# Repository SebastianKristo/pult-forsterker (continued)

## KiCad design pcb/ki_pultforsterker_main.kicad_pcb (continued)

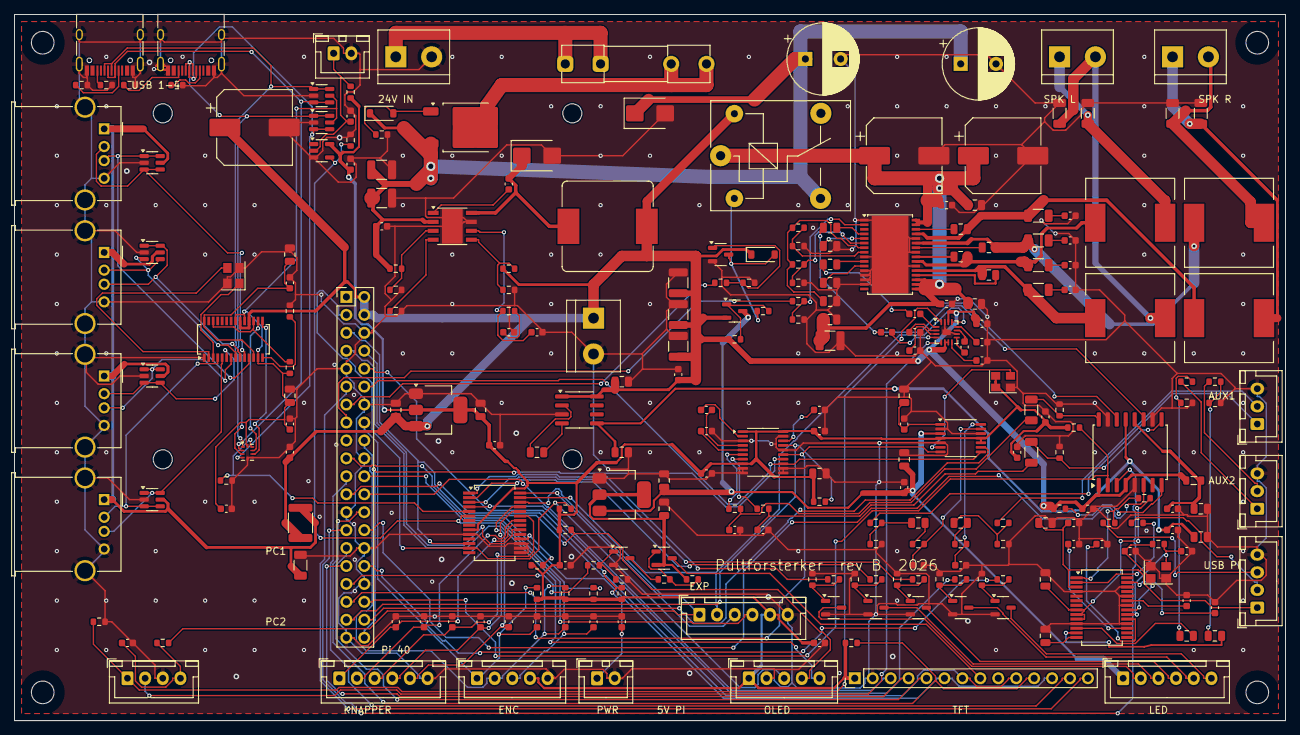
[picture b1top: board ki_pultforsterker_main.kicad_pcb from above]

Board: 2 copper layers, 180.0 x 100.0 mm, 264 parts (0 on the bottom side), 188 nets.

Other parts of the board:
H1, H2, H3, H4: M3; MountingHole_3.2mm_M3
H5, H6, H7, H8: M2.5; MountingHole_2.7mm_M2.5

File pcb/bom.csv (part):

Designator,Value,Footprint,LCSC,Beskrivelse
J1,24V IN,TerminalBlock_bornier-2_P5.08mm,C8465,"24 V inn fra DC-099 via KCD1 (skruterminal 5,08)"
F1,5A 5x20 (Littelfuse 111-klips),Fuseholder_Clip-5x20mm_Littelfuse_111_Inline_P20.00x5.00mm_D1.05mm_Horizontal,C151075,"Sikringsholder 5x20 (klips, THT) + sikring 5 A"
D1,SMBJ28A,D_SMB,C20623778,"TVS 28 V standoff, klemmer ~45 V (LCSC-kode sjekkes i BOM-verktøyet)"
Q11,AOD409,TO-252-2,C36220,"Polvendingsvern i 24 V-linjen (D = inn, S = ut, G mot GND) – velg TO-252 P-kanal ≥ 60 V i JLC-verktøyet"
D5,BZT52C12,D_SOD-123,C43491,Zener gate-source Q11
R79,100k,R_0603_1608Metric,C25803,Gate Q11 mot GND
C1,680-1000u/35V 10x16,CP_Radial_D10.0mm_P5.00mm,,"Bulk elektrolytt Ø10 × maks 16 mm (THT, loddes selv)"
C110,680-1000u/35V 10x16,CP_Radial_D10.0mm_P5.00mm,,Bulk elektrolytt nr. 2 (Ø10 × maks 16 mm)
J2,SPK L,TerminalBlock_bornier-2_P5.08mm,C8465,Høyttaler venstre + / -
J3,SPK R,TerminalBlock_bornier-2_P5.08mm,C8465,Høyttaler høyre + / -
K1,SRD-05VDC-SL-C,Relay_SPDT_SANYOU_SRD_Series_Form_C,C35449,"Relé 10 A: bryter 24 V til forsterkeren (KiCad-pads: 2+5 spole, 1 COM, 3 NO, 4 NC – mål før første gang!)"
Q7,AO3400A,SOT-23-3,C20917,Relédriver + styrer Q8
D4,1N4148W,D_SOD-123,C81598,Flyback relé
R52,100,R_0603_1608Metric,C22775,Gate Q7
R53,100k,R_0603_1608Metric,C25803,Gate pulldown Q7
Q8,AO3401A,SOT-23-3,C15127,P-MOSFET 5 V -> 5V_SW
R54,10k,R_0603_1608Metric,C25804,Q8 gate fra Q7
R55,100k,R_0603_1608Metric,C25803,Q8 gate pull-up
U1,TPS54560DDAR,Texas_HSOP-8-1EP_3.9x4.9mm_P1.27mm,C31966,Buck 60 V 5 A
C2,4.7u/50V,C_1210_3225Metric,C170099,Cin
C3,4.7u/50V,C_1210_3225Metric,C170099,Cin
C4,100n/50V,C_0603_1608Metric,C14663,Cin HF
C5,100n/50V,C_0603_1608Metric,C14663,Boot
R1,330k,R_0603_1608Metric,C23137,EN divider (UVLO ~9 V)
R2,49.9k,R_0603_1608Metric,C23184,EN divider
R3,243k,R_0603_1608Metric,C100895,RT 400 kHz
R4,33k,R_0603_1608Metric,C4216,"FB top (33k/6,2k -> 5,06 V)"
R5,6.2k,R_0603_1608Metric,C4260,"FB bottom (5,06 V)"
R6,13k,R_0603_1608Metric,C22797,Comp R
C6,3.3n,C_0603_1608Metric,C1613,Comp C
C7,47p,C_0603_1608Metric,C1671,Comp Cp
L1,10uH 6A SRP1245A-100M,L_Bourns_SRP1245A,C2042471,Buck-spole 10 µH – Bourns SRP1245A-100M (søk i JLC-UI; alternativ: CEC SMRH125-100M C241221 4 A på samme fotavtrykk)
D2,SS56,D_SMB,C4154973,Catch-diode 60 V 5 A
C8,47u/16V,C_1210_3225Metric,C77101,Cout
C9,47u/16V,C_1210_3225Metric,C77101,Cout
C10,47u/16V,C_1210_3225Metric,C77101,Cout
C11,100n/50V,C_0603_1608Metric,C14663,Cout HF
U2,AMS1117-3.3,SOT-223-3_TabPin2,C6186,"LDO 3,3 V (alltid på: MCP23017, pull-ups)"
C12,10u,C_0805_2012Metric,C15850,LDO in
C13,10u,C_0805_2012Metric,C15850,LDO out
C14,100n/50V,C_0603_1608Metric,C14663,LDO out HF
U3,LM2662MX,SOIC-8_3.9x4.9mm_P1.27mm,C129316,"Ladepumpe -5 V, 150 kHz (FC til V+), 200 mA"
C15,10u,C_0805_2012Metric,C15850,Flykondensator
C109,10u,C_0805_2012Metric,C15850,LM2662 inn
C16,10u,C_0805_2012Metric,C15850,-5 V ut
U9,AMS1117-3.3,SOT-223-3_TabPin2,C6186,"LDO 3,3 V_SW (DAC, ADC, OLED/TFT) fra 5V_SW"
C75,10u,C_0805_2012Metric,C15850,LDO_SW in
C76,10u,C_0805_2012Metric,C15850,LDO_SW out
J5,RPi 40-pin,PinHeader_2x20_P2.54mm_Vertical,C50980,Raspberry Pi 40-pin (flatkabel)
J6,5V -> PI,TerminalBlock_bornier-2_P5.08mm,C8465,"5 V til Pi 4 (18 AWG til header pinne 2/6). Står med pinnene i x = 82 – utenfor Pi-ens USB3-blokk (x 84,5–104,5 under kortet)"
U12,MCP23017-E/SS,SSOP-28_5.3x10.2mm_P0.65mm,C506653,"I2C I/O-ekspander 0x20: knapper, LED-ringer, USB-mux"
R56,10k,R_0603_1608Metric,C25804,MCP RESET pull-up
C74,100n/50V,C_0603_1608Metric,C14663,MCP VDD
R43,4.7k,R_0603_1608Metric,C23162,I2C pull-up SDA
R44,4.7k,R_0603_1608Metric,C23162,I2C pull-up SCL
U4,PCM5102APWR,TSSOP-20_4.4x6.5mm_P0.65mm,C107671,I2S-DAC
C17,2.2u,C_0603_1608Metric,C23630,CAPP-CAPM
C18,2.2u,C_0603_1608Metric,C23630,VNEG
C19,2.2u,C_0603_1608Metric,C23630,LDOO
C20,100n/50V,C_0603_1608Metric,C14663,DVDD
C21,100n/50V,C_0603_1608Metric,C14663,AVDD/CPVDD
C22,10u,C_0805_2012Metric,C15850,3V3 bulk DAC
R7,10k,R_0603_1608Metric,C25804,XSMT pull-up
R8,100,R_0603_1608Metric,C22775,DAC L serie
R9,100,R_0603_1608Metric,C22775,DAC R serie
C23,2.2n/50V,C_0603_1608Metric,C1604,DAC L LP
C24,2.2n/50V,C_0603_1608Metric,C1604,DAC R LP
U10,PCM1808PWR,TSSOP-14_4.4x5mm_P0.65mm,C55513,"I2S-ADC AUX 1, master 256 fs (MD1=MD0=1, FMT=0)"
X1,12.288MHz,Oscillator_SMD_Abracon_ASE-4Pin_3.2x2.5mm,C437124,"Oscillator 3,3 V -> SCKI (48 kHz)"
C77,100n/50V,C_0603_1608Metric,C14663,Osc VDD
C78,10u,C_0805_2012Metric,C15850,VREF
C79,100n/50V,C_0603_1608Metric,C14663,VREF HF
C80,10u,C_0805_2012Metric,C15850,ADC VCC
C81,100n/50V,C_0603_1608Metric,C14663,ADC VCC HF
C82,100n/50V,C_0603_1608Metric,C14663,ADC VDD
R57,10k,R_0603_1608Metric,C25804,AUX1 L deler
R58,10k,R_0603_1608Metric,C25804,AUX1 L deler GND
R59,10k,R_0603_1608Metric,C25804,AUX1 R deler
R60,10k,R_0603_1608Metric,C25804,AUX1 R deler GND
C83,4.7u,C_0805_2012Metric,C1779,AUX1 L kobling
C84,4.7u,C_0805_2012Metric,C1779,AUX1 R kobling
R61,1k,R_0603_1608Metric,C21190,AUX1 L serie
R62,1k,R_0603_1608Metric,C21190,AUX1 R serie
C85,1n,C_0603_1608Metric,C1588,AUX1 L LP
C86,1n,C_0603_1608Metric,C1588,AUX1 R LP
C25,10u,C_1206_3216Metric,C13585,Kobling L
C26,10u,C_1206_3216Metric,C13585,Kobling R
R12,100k,R_0603_1608Metric,C25803,Bias L
R13,100k,R_0603_1608Metric,C25803,Bias R
U5,PGA2311UA,SOIC-16W_7.5x10.3mm_P1.27mm,C486061,Volumkontroll ±5 V
C27,100n/50V,C_0603_1608Metric,C14663,VD+
C28,100n/50V,C_0603_1608Metric,C14663,VA+
C29,100n/50V,C_0603_1608Metric,C14663,VA-
C30,10u,C_0805_2012Metric,C15850,VA+ bulk
C31,10u,C_0805_2012Metric,C15850,VA- bulk
FB1,600R@100MHz,L_0805_2012Metric,C18305,Ferritt 5V_SW -> PGA2311 VA+ (filter)
R14,10k,R_0603_1608Metric,C25804,MUTE pull-up
U6,TPA3116D2DADR,HTSSOP-32-1EP_6.1x11mm_P0.65mm_EP5.2x11mm_Mask4.11x4.36mm,C50144,Klasse D 2x50 W (kjøleflate på toppen – kjøleribbe!)
C32,220n/50V,C_0805_2012Metric,C5378,"BSNL (snudd: OUTNL rett inn i pad 2, BSNL rundt under)"
C33,220n/50V,C_0805_2012Metric,C5378,BSPL
C34,220n/50V,C_0805_2012Metric,C5378,BSNR
C35,220n/50V,C_0805_2012Metric,C5378,BSPR
C36,100n/50V,C_0603_1608Metric,C14663,PVCC HF
C37,1u/50V,C_0805_2012Metric,C28323,PVCC
C38,100n/50V,C_0603_1608Metric,C14663,PVCC HF
C39,1u/50V,C_0805_2012Metric,C28323,PVCC
C40,220u/50V,CP_Elec_10x10.5,C190286,PVCC bulk
C41,220u/50V,CP_Elec_10x10.5,C190286,PVCC bulk
C42,1u/50V,C_0805_2012Metric,C28323,AVCC
C43,4.7u/50V,C_1210_3225Metric,C170099,AVCC bulk
C44,1u/50V,C_0805_2012Metric,C28323,GVDD
R15,100k,R_0603_1608Metric,C25803,GAIN top
R16,20k,R_0603_1608Metric,C4184,GAIN bottom (26 dB)
R17,0R,R_0603_1608Metric,C21189,PLIMIT -> GVDD (ingen begrensning)
R18,DNP,R_0603_1608Metric,,PLIMIT til GND (valgfri)
R19,1k,R_0603_1608Metric,C21190,SDZ serie
R20,100k,R_0603_1608Metric,C25803,SDZ pulldown
C45,1u/50V,C_0805_2012Metric,C28323,LINP kobling
C46,1u/50V,C_0805_2012Metric,C28323,LINN til GND
C47,1u/50V,C_0805_2012Metric,C28323,RINP kobling
C48,1u/50V,C_0805_2012Metric,C28323,RINN til GND
L2,10uH 5.5A,L_12x12mm_H8mm,C3221699,Utgangsfilter OUTNL
L3,10uH 5.5A,L_12x12mm_H8mm,C3221699,Utgangsfilter OUTPL
L4,10uH 5.5A,L_12x12mm_H8mm,C3221699,Utgangsfilter OUTNR
L5,10uH 5.5A,L_12x12mm_H8mm,C3221699,Utgangsfilter OUTPR
C49,680n/50V,C_1206_3216Metric,C1881,Filter OUTNL
C50,680n/50V,C_1206_3216Metric,C1881,Filter OUTPL
C51,680n/50V,C_1206_3216Metric,C1881,Filter OUTNR
C52,680n/50V,C_1206_3216Metric,C1881,Filter OUTPR
R21,18R,R_1206_3216Metric,C2907439,Snubber NL
C53,330p/50V,C_0603_1608Metric,C1664,Snubber NL
R22,18R,R_1206_3216Metric,C2907439,Snubber PL
C54,330p/50V,C_0603_1608Metric,C1664,Snubber PL
R23,18R,R_1206_3216Metric,C2907439,Snubber NR
C55,330p/50V,C_0603_1608Metric,C1664,Snubber NR
R24,18R,R_1206_3216Metric,C2907439,Snubber PR
C56,330p/50V,C_0603_1608Metric,C1664,Snubber PR
U11,PCM2900CDB,SSOP-28_5.3x10.2mm_P0.65mm,C180425,USB-lydkodek AUX 2 (ADC)
Y2,12MHz,Crystal_SMD_3225-4Pin_3.2x2.5mm,C9002,Kodek-krystall
C87,22p,C_0603_1608Metric,C1653,XTI last
C88,22p,C_0603_1608Metric,C1653,XTO last
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
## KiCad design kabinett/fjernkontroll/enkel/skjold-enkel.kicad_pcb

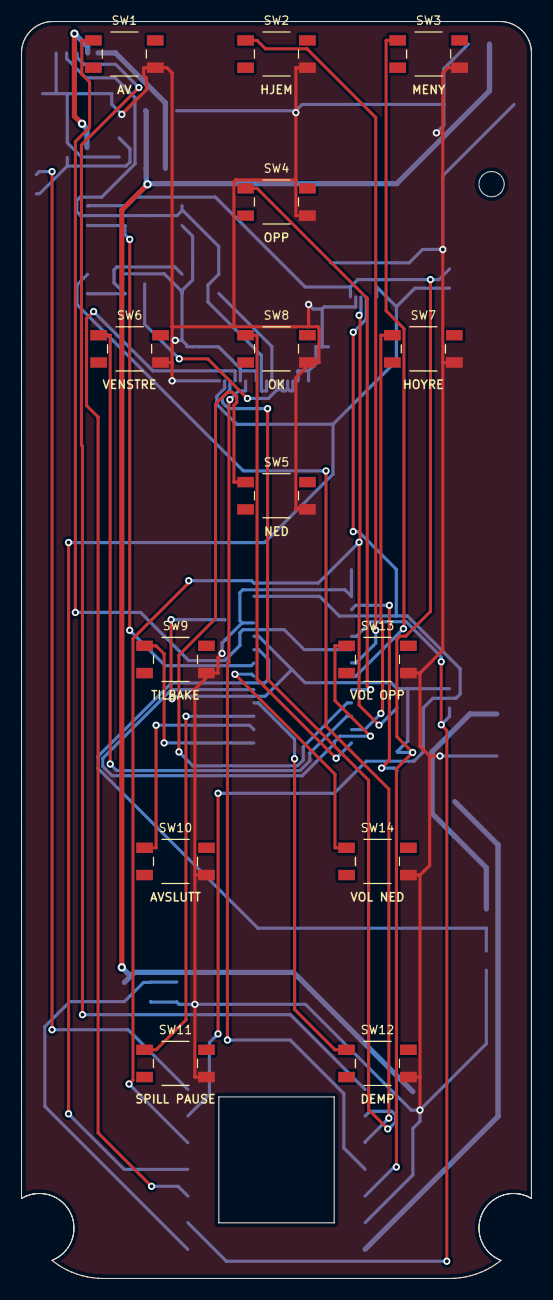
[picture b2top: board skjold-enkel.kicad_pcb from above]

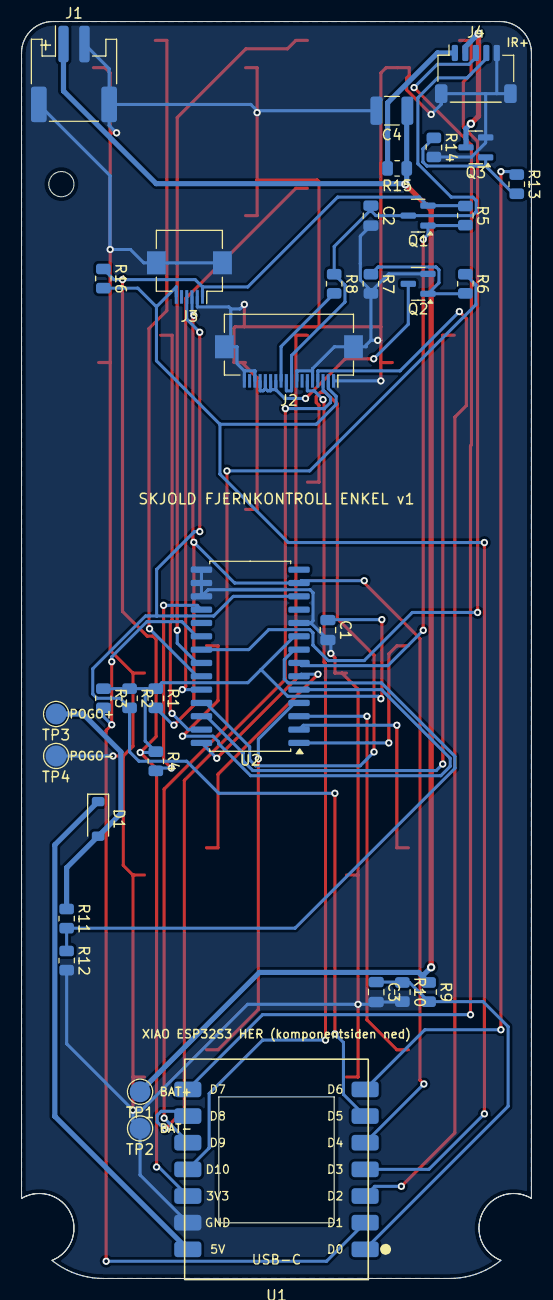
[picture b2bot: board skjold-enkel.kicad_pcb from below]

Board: 2 copper layers, 48.6 x 119.8 mm, 48 parts (34 on the bottom side), 40 nets.

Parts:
C1, C3: 100nF; C_0805_2012Metric
C2: 10uF; C_0805_2012Metric
C4: 100uF; C_1210_3225Metric
D1: B5819W; D_SOD-123
J1: S2B-PH-SM4-TB; JST_PH_S2B-PH-SM4-TB_1x02-1MP_P2.00mm_Horizontal
J2: FH12-18S-0.5SH; Hirose_FH12-18S-0.5SH_1x18-1MP_P0.50mm_Horizontal
J3: FH12-6S-0.5SH; Hirose_FH12-6S-0.5SH_1x06-1MP_P0.50mm_Horizontal
J4: SM05B-SRSS-TB; JST_SH_SM05B-SRSS-TB_1x05-1MP_P1.00mm_Horizontal
Q1: AO3401A; SOT-23
Q2, Q3: AO3400A; SOT-23
R1, R2: 4.7k; R_0805_2012Metric
R3, R4: 10k; R_0805_2012Metric
R5, R7, R12, R14: 100k; R_0805_2012Metric
R6, R13: 100R; R_0805_2012Metric
R8: 10R; R_0805_2012Metric
R9, R10, R16: 1M; R_0805_2012Metric
R11: 68k; R_0805_2012Metric
R15: 6.8R; R_0805_2012Metric
SW1, SW2, SW3, SW4, SW5, SW6, SW7, SW8, SW9, SW10, SW11, SW12, SW13, SW14: 4x4x1.5; SW_Tact_4x4x1.5mm_SMD
TP1: BAT+; TestPoint_Pad_D2.0mm
TP2: BAT-; TestPoint_Pad_D2.0mm
TP3: POGO+; TestPoint_Pad_D2.0mm
TP4: POGO-; TestPoint_Pad_D2.0mm
U1: XIAO_ESP32S3; Seeed_XIAO_ESP32S3_SMD
U2: MCP23017-E/SO; SOIC-28W_7.5x17.9mm_P1.27mm

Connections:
3V3: C1.1, J3.1, Q1.2, R1.1, R2.1, R3.1, R4.1, R5.1, R16.1, U1.12, U2.9
3V3_SW: C2.1, J2.9, J2.10, J4.4, Q1.3, R8.1
BL_G: Q2.1, R6.2, R7.1
DOKK: R11.2, R12.1, U2.8
GND: C1.2, C2.2, C3.2, C4.2, J1.2, J1.MP, J2.1, J2.5, J2.8, J2.16, J2.18, J2.MP, J3.2, J3.MP, J4.5, J4.MP, Q2.2, Q3.2, R7.2, R10.2, R12.2, R14.2, SW1.2, SW2.2, SW3.2, SW4.2, SW5.2, SW6.2, SW7.2, SW8.2, SW9.2, SW10.2, SW11.2, SW12.2, SW13.2, SW14.2, TP2.1, TP4.1, U1.13, U2.10, U2.15, U2.16, U2.17
INT: R3.2, U1.2, U2.20
IR_A: J4.1, R15.2
IR_G: Q3.1, R13.2, R14.1
IR_K: J4.2, Q3.3
IR_RX: J4.3, U1.8
IR_TX: R13.1, U1.7
K_AV: SW1.1, U2.21
K_AVSLUTT: SW10.1, U2.2
K_DEMP: SW12.1, U2.4
K_HJEM: SW2.1, U2.22
K_HOYRE: SW7.1, U2.27
K_MENY: SW3.1, U2.23
K_NED: SW5.1, U2.25
K_OK: SW8.1, U2.28
K_OPP: SW4.1, U2.24
K_SPILL_PAUSE: SW11.1, U2.3
K_TILBAKE: SW9.1, U2.1
K_VENSTRE: SW6.1, U2.26
K_VOL_NED: SW14.1, U2.6
K_VOL_OPP: SW13.1, U2.5
LCD_BL: R6.1, U1.10
LCD_DC: J2.4, U1.3
LCD_MOSI: J2.6, U1.11
LCD_RES: J2.2, J3.6, R16.2, U1.4
LCD_SCK: J2.3, U1.9
LED_A: J2.11, R8.2
LED_K: J2.12, J2.13, J2.14, J2.15, Q2.3
MCP_RST: R4.2, U2.18
POGO: D1.2, R11.1, TP3.1
SCL: J3.4, R2.2, U1.6, U2.12
SDA: J3.3, R1.2, U1.5, U2.13
SKJ: Q1.1, R5.2, U2.7
VBAT: C4.1, J1.1, R9.1, R15.1, TP1.1
VBAT_ADC: C3.1, R9.2, R10.1, U1.1
VBUS: D1.1, U1.14

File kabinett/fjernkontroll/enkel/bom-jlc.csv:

Comment,Designator,Footprint,LCSC Part #
100nF,"C1,C3",C_0805_2012Metric,C49678 (sjekk)
10uF,C2,C_0805_2012Metric,C15850 (sjekk)
100uF,C4,C_1210_3225Metric,sjekk: søk «100uF C»
B5819W,D1,D_SOD-123,C8598 (sjekk)
S2B-PH-SM4-TB,J1,JST_PH_S2B-PH-SM4-TB_1x02-1MP_P2.00mm_Horizontal,sjekk: søk «S2B-PH-SM4-TB JST»
FH12-18S-0.5SH,J2,Hirose_FH12-18S-0.5SH_1x18-1MP_P0.50mm_Horizontal,sjekk: søk «FH12-18S-0.5SH Hirose»
FH12-6S-0.5SH,J3,Hirose_FH12-6S-0.5SH_1x06-1MP_P0.50mm_Horizontal,sjekk: søk «FH12-6S-0.5SH Hirose»
SM05B-SRSS-TB,J4,JST_SH_SM05B-SRSS-TB_1x05-1MP_P1.00mm_Horizontal,sjekk: søk «SM05B-SRSS-TB JST»
AO3401A,Q1,SOT-23,C15127 (sjekk)
AO3400A,"Q2,Q3",SOT-23,C20917 (sjekk)
4.7k,"R1,R2",R_0805_2012Metric,C17673 (sjekk)
68k,R11,R_0805_2012Metric,C17801 (sjekk)
100k,"R5,R7,R12,R14",R_0805_2012Metric,C17407 (sjekk)
100R,"R6,R13",R_0805_2012Metric,C17408 (sjekk)
6.8R,R15,R_0805_2012Metric,sjekk: søk «6.8R R»
10k,"R3,R4",R_0805_2012Metric,C17414 (sjekk)
10R,R8,R_0805_2012Metric,C17415 (sjekk)
1M,"R9,R10,R16",R_0805_2012Metric,C17514 (sjekk)
MCP23017-E/SO,U2,SOIC-28W_7.5x17.9mm_P1.27mm,sjekk: søk «MCP23017-E/SO SOIC-28W»

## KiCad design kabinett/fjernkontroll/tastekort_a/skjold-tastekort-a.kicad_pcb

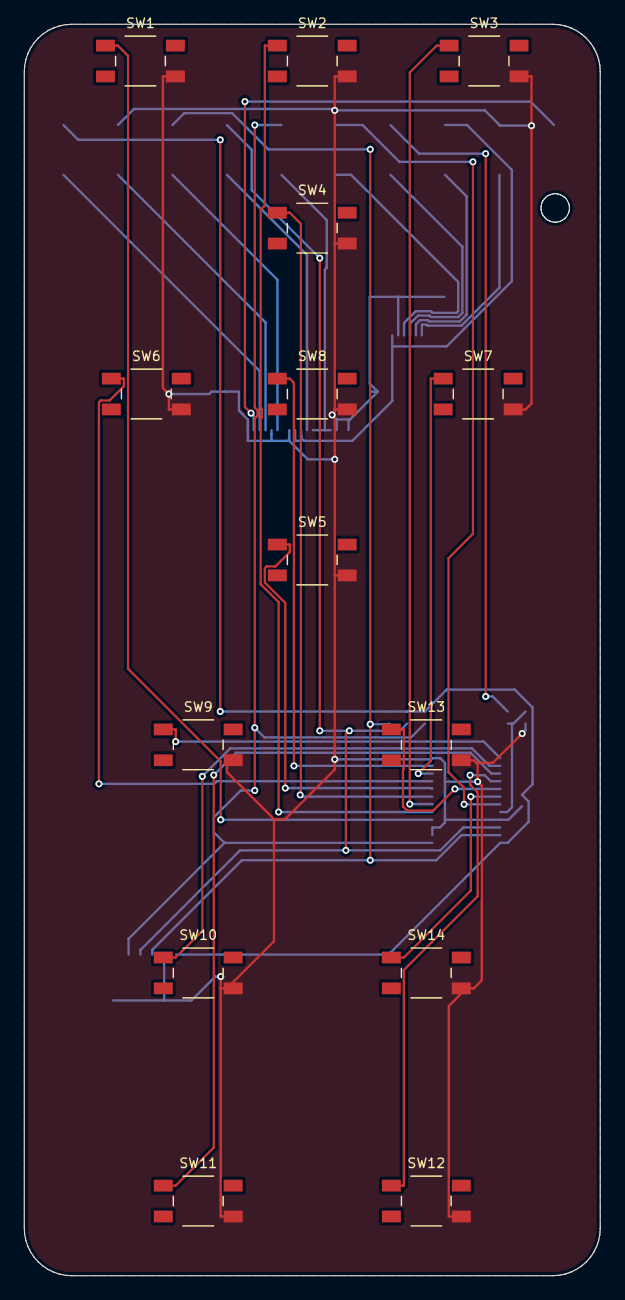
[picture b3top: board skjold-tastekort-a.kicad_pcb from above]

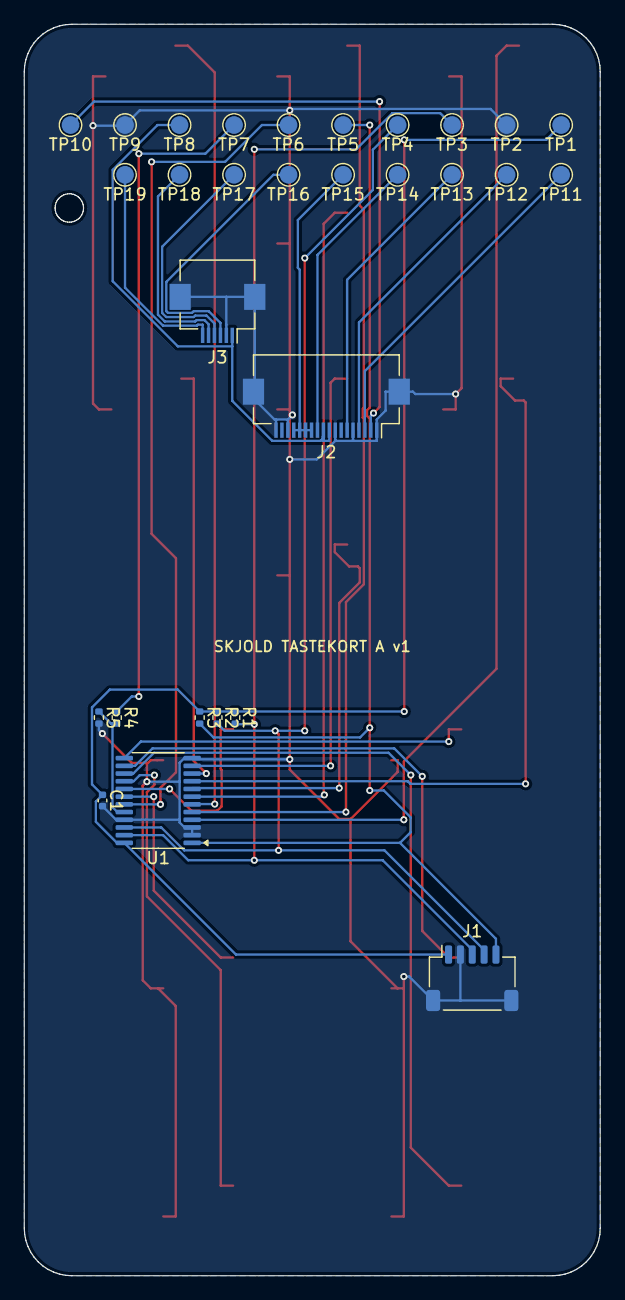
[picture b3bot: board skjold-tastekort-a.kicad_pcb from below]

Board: 2 copper layers, 48.6 x 105.6 mm, 43 parts (29 on the bottom side), 33 nets.

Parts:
C1: 100nF; C_0402_1005Metric
J1: SM05B-SRSS-TB; JST_SH_SM05B-SRSS-TB_1x05-1MP_P1.00mm_Horizontal
J2: FH12-18S-0.5SH; Hirose_FH12-18S-0.5SH_1x18-1MP_P0.50mm_Horizontal
J3: FH12-6S-0.5SH; Hirose_FH12-6S-0.5SH_1x06-1MP_P0.50mm_Horizontal
R1, R2, R3: 10k; R_0402_1005Metric
R4: 68k; R_0402_1005Metric
R5: 100k; R_0402_1005Metric
SW1, SW2, SW3, SW4, SW5, SW6, SW7, SW8, SW9, SW10, SW11, SW12, SW13, SW14: 4x4x1.5; SW_Tact_4x4x1.5mm_SMD
TP1: 3V3; TestPoint_Pad_D1.5mm
TP2, TP9: GND; TestPoint_Pad_D1.5mm
TP3: SDA; TestPoint_Pad_D1.5mm
TP4: SCL; TestPoint_Pad_D1.5mm
TP5: INT; TestPoint_Pad_D1.5mm
TP6: SKJ; TestPoint_Pad_D1.5mm
TP7: POGO+; TestPoint_Pad_D1.5mm
TP8: VCC; TestPoint_Pad_D1.5mm
TP10: LCD_RES; TestPoint_Pad_D1.5mm
TP11: LCD_SCK; TestPoint_Pad_D1.5mm
TP12: LCD_DC; TestPoint_Pad_D1.5mm
TP13: LCD_MOSI; TestPoint_Pad_D1.5mm
TP14: LED_A; TestPoint_Pad_D1.5mm
TP15: LED_K; TestPoint_Pad_D1.5mm
TP16: T_SDA; TestPoint_Pad_D1.5mm
TP17: T_SCL; TestPoint_Pad_D1.5mm
TP18: T_INT; TestPoint_Pad_D1.5mm
TP19: T_RST; TestPoint_Pad_D1.5mm
U1: TCA9555PWR; TSSOP-24_4.4x7.8mm_P0.65mm

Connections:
3V3: C1.1, J1.1, R1.1, R2.1, R3.1, TP1.1, U1.24
DOKK: R4.2, R5.1, U1.20
GND: C1.2, J1.2, J1.MP, J2.1, J2.5, J2.8, J2.16, J2.18, J2.MP, J3.2, J3.MP, R5.2, SW1.2, SW2.2, SW3.2, SW4.2, SW5.2, SW6.2, SW7.2, SW8.2, SW9.2, SW10.2, SW11.2, SW12.2, SW13.2, SW14.2, TP2.1, TP9.1, U1.2, U1.3, U1.12, U1.21
INT: J1.5, R3.2, TP5.1, U1.1
K_AV: SW1.1, U1.4
K_AVSLUTT: SW10.1, U1.14
K_DEMP: SW12.1, U1.16
K_HJEM: SW2.1, U1.5
K_HOYRE: SW7.1, U1.10
K_MENY: SW3.1, U1.6
K_NED: SW5.1, U1.8
K_OK: SW8.1, U1.11
K_OPP: SW4.1, U1.7
K_SPILL_PAUSE: SW11.1, U1.15
K_TILBAKE: SW9.1, U1.13
K_VENSTRE: SW6.1, U1.9
K_VOL_NED: SW14.1, U1.18
K_VOL_OPP: SW13.1, U1.17
LCD_DC: J2.4, TP12.1
LCD_MOSI: J2.6, TP13.1
LCD_RES: J2.2, TP10.1
LCD_SCK: J2.3, TP11.1
LED_A: J2.11, TP14.1
LED_K: J2.12, J2.13, J2.14, J2.15, TP15.1
POGO: R4.1, TP7.1
SCL: J1.4, R2.2, TP4.1, U1.22
SDA: J1.3, R1.2, TP3.1, U1.23
SKJ: TP6.1, U1.19
T_INT: J3.5, TP18.1
T_RST: J3.6, TP19.1
T_SCL: J3.4, TP17.1
T_SDA: J3.3, TP16.1
VCC_SKJ: J2.9, J2.10, J3.1, TP8.1

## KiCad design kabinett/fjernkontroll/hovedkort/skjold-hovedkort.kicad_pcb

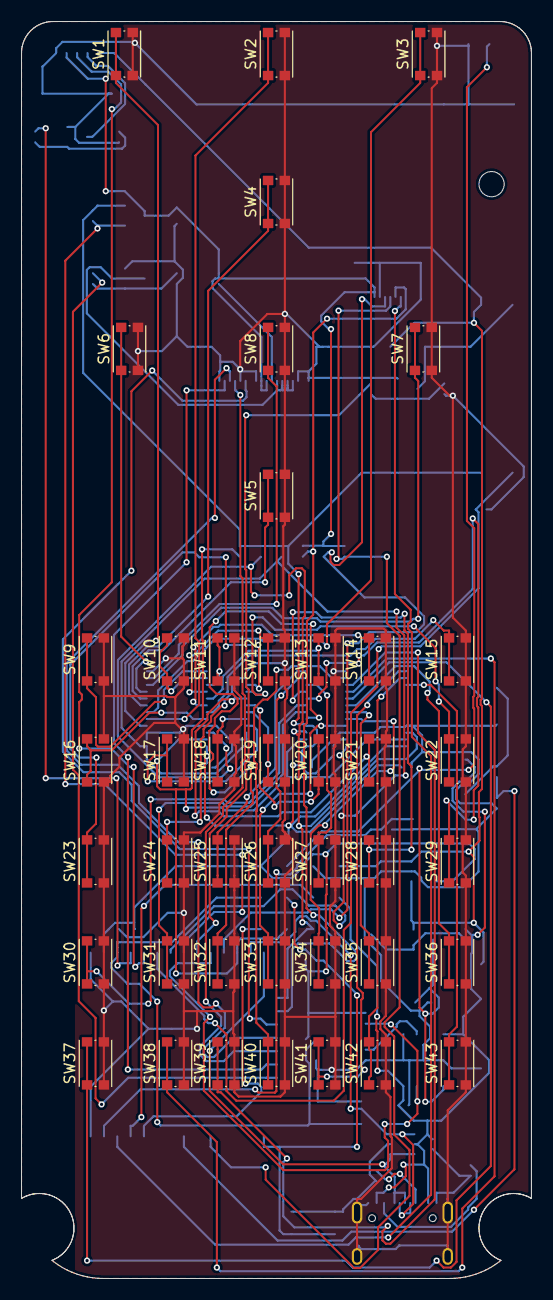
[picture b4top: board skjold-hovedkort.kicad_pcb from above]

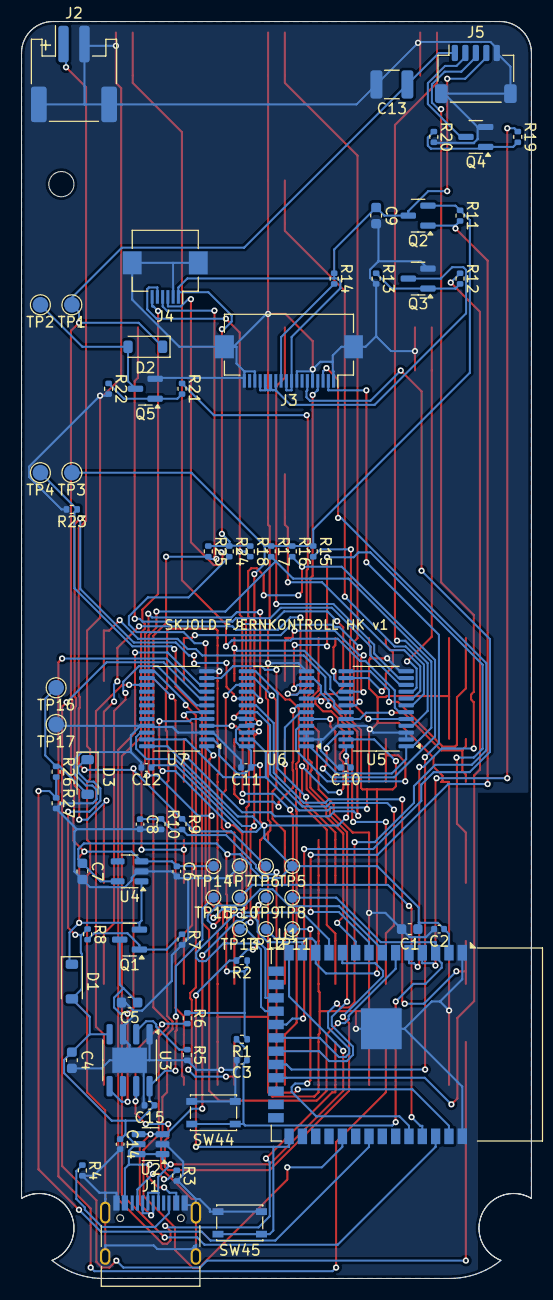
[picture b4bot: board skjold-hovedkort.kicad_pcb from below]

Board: 2 copper layers, 48.6 x 119.8 mm, 124 parts (81 on the bottom side), 87 nets.

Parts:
C1, C4, C5, C7, C9: 10uF; C_0603_1608Metric
C2, C8, C10, C11, C12, C14, C15: 100nF; C_0402_1005Metric
C3, C6: 1uF; C_0402_1005Metric
C13: 100uF; C_1210_3225Metric
D1, D2, D3: B5819W; D_SOD-123
J1: TYPE-C-31-M-12; USB_C_Receptacle_HRO_TYPE-C-31-M-12
J2: S2B-PH-SM4-TB; JST_PH_S2B-PH-SM4-TB_1x02-1MP_P2.00mm_Horizontal
J3: FH12-18S-0.5SH; Hirose_FH12-18S-0.5SH_1x18-1MP_P0.50mm_Horizontal
J4: FH12-6S-0.5SH; Hirose_FH12-6S-0.5SH_1x06-1MP_P0.50mm_Horizontal
J5: SM05B-SRSS-TB; JST_SH_SM05B-SRSS-TB_1x05-1MP_P1.00mm_Horizontal
Q1, Q2: AO3401A; SOT-23
Q3, Q4, Q5: AO3400A; SOT-23
R1, R2, R6, R17, R18: 10k; R_0402_1005Metric
R3, R4: 5.1k; R_0402_1005Metric
R5: 2.4k; R_0402_1005Metric
R7, R11, R13, R20, R22, R27: 100k; R_0402_1005Metric
R8: 0R; R_0402_1005Metric
R9, R10, R23: 1M; R_0402_1005Metric
R12, R19: 100R; R_0402_1005Metric
R14: 10R; R_0402_1005Metric
R15, R16, R24, R25: 4.7k; R_0402_1005Metric
R21: 1k; R_0402_1005Metric
R26: 68k; R_0402_1005Metric
SW1, SW2, SW3, SW4, SW5, SW6, SW7, SW8, SW9, SW10, SW11, SW12, SW13, SW14, SW15, SW16, SW17, SW18, SW19, SW20, SW21, SW22, SW23, SW24, SW25, SW26, SW27, SW28, SW29, SW30, SW31, SW32, SW33, SW34, SW35, SW36, SW37, SW38, SW39, SW40, SW41, SW42, SW43: KMR221G; SW_Push_1P1T_NO_CK_KMR2
SW44: PTS810 RESET; SW_SPST_PTS810
SW45: PTS810 BOOT; SW_SPST_PTS810
TP1: MOT+; TestPoint_Pad_D1.5mm
TP2: MOT-; TestPoint_Pad_D1.5mm
TP3: VIB 3V3; TestPoint_Pad_D1.5mm
TP4: VIB; TestPoint_Pad_D1.5mm
TP5: 3V3; TestPoint_Pad_D1.0mm
TP6: VBAT; TestPoint_Pad_D1.0mm
TP7: GND; TestPoint_Pad_D1.0mm
TP8: EN; TestPoint_Pad_D1.0mm
TP9: BOOT; TestPoint_Pad_D1.0mm
TP10: U0TXD; TestPoint_Pad_D1.0mm
TP11: U0RXD; TestPoint_Pad_D1.0mm
TP12: SDA; TestPoint_Pad_D1.0mm
TP13: SCL; TestPoint_Pad_D1.0mm
TP14: VSYS; TestPoint_Pad_D1.0mm
TP15: VBUS; TestPoint_Pad_D1.0mm
TP16: POGO+; TestPoint_Pad_D1.5mm
TP17: POGO-; TestPoint_Pad_D1.5mm
U1: ESP32-S3-WROOM-1-N4R2; ESP32-S3-WROOM-1
U2: USBLC6-2SC6; SOT-23-6
U3: TP4056; SOIC-8-1EP_3.9x4.9mm_P1.27mm_EP2.41x3.3mm
U4: RT9080-33GJ5; SOT-23-5
U5, U6, U7: TCA9555PWR; TSSOP-24_4.4x7.8mm_P0.65mm

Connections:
3V3: C1.1, C2.1, C7.1, C10.1, C11.1, C12.1, Q2.2, R1.1, R2.1, R6.1, R11.1, R15.1, R16.1, R17.1, TP3.1, TP5.1, U1.2, U4.5, U5.24, U6.21, U6.24, U7.2, U7.24
3V3_SW: C9.1, J3.9, J3.10, J4.1, J5.4, Q2.3, R14.1, R18.1, R24.1, R25.1
BL_G: Q3.1, R12.2, R13.1
BOOT: R2.2, SW45.1, TP9.1, U1.27
CC1: J1.A5, R3.1
CC2: J1.B5, R4.1
CHRG: R6.2, U1.10, U3.7
DOKK: R26.2, R27.1, U1.33
EN: C3.1, R1.2, SW44.1, TP8.1, U1.3
GND: C1.2, C2.2, C3.2, C4.2, C5.2, C6.2, C7.2, C8.2, C9.2, C10.2, C11.2, C12.2, C13.2, C14.2, C15.2, J1.A1, J1.A12, J1.B1, J1.B12, J1.S1, J2.2, J2.MP, J3.1, J3.5, J3.8, J3.16, J3.18, J3.MP, J4.2, J4.MP, J5.5, J5.MP, Q3.2, Q4.2, Q5.2, R3.2, R4.2, R5.2, R7.2, R10.2, R13.2, R20.2, R22.2, R23.2, R27.2, SW1.2, SW2.2, SW3.2, SW4.2, SW5.2, SW6.2, SW7.2, SW8.2, SW9.2, SW10.2, SW11.2, SW12.2, SW13.2, SW14.2, SW15.2, SW16.2, SW17.2, SW18.2, SW19.2, SW20.2, SW21.2, SW22.2, SW23.2, SW24.2, SW25.2, SW26.2, SW27.2, SW28.2, SW29.2, SW30.2, SW31.2, SW32.2, SW33.2, SW34.2, SW35.2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
IR_G: Q4.1, R19.2, R20.1
IR_K: J5.2, Q4.3
IR_RX: J5.3, U1.5
IR_TX: R19.1, U1.4
K_av: SW1.1, U5.4
K_g00: SW9.1, U5.13
K_g01: SW10.1, U5.14
K_g02: SW11.1, U5.15
K_g03: SW12.1, U5.16
K_g04: SW13.1, U5.17
K_g05: SW14.1, U5.18
K_g06: SW15.1, U5.19
K_g07: SW16.1, U5.20
K_g08: SW17.1, U6.4
K_g09: SW18.1, U6.5
K_g10: SW19.1, U6.6
K_g11: SW20.1, U6.7
K_g12: SW21.1, U6.8
K_g13: SW22.1, U6.9
K_g14: SW23.1, U6.10
K_g15: SW24.1, U6.11
K_g16: SW25.1, U6.13
K_g17: SW26.1, U6.14
K_g18: SW27.1, U6.15
K_g19: SW28.1, U6.16
K_g20: SW29.1, U6.17
K_g21: SW30.1, U6.18
K_g22: SW31.1, U6.19
K_g23: SW32.1, U6.20
K_g24: SW33.1, U7.4
K_g25: SW34.1, U7.5
K_g26: SW35.1, U7.6
K_g27: SW36.1, U7.7
K_g28: SW37.1, U7.8
K_g29: SW38.1, U7.9
K_g30: SW39.1, U7.10
K_g31: SW40.1, U7.11
K_g32: SW41.1, U7.13
K_g33: SW42.1, U7.14
K_g34: SW43.1, U7.15
K_hjem: SW2.1, U5.5
K_hoyre: SW7.1, U5.10
K_meny: SW3.1, U5.6
K_ned: SW5.1, U5.8
K_ok: SW8.1, U5.11
K_opp: SW4.1, U5.7
K_venstre: SW6.1, U5.9
LCD_BL: R12.1, U1.23
LCD_DC: J3.4, U1.21
LCD_MOSI: J3.6, U1.19
LCD_RES: J3.2, U1.22
LCD_SCK: J3.3, U1.20
LED_A: J3.11, R14.2
LED_K: J3.12, J3.13, J3.14, J3.15, Q3.3
MOTOR: R21.1, U1.9
MOT_G: Q5.1, R21.2, R22.1
MOT_K: D2.2, Q5.3, TP2.1
POGO: D3.2, R26.1, TP16.1
PROG: R5.1, U3.2
SCL: R16.2, TP13.1, U1.17, U5.22, U6.22, U7.22
SDA: R15.2, TP12.1, U1.12, U5.23, U6.23, U7.23
SKJ_PA: Q2.1, R11.2, U1.8
TCA_INT: R17.2, U1.7, U5.1, U6.1, U7.1
T_INT: J4.5, R18.2, U1.18
T_RST: J4.6, U1.38
T_SCL: J4.4, R25.2, U1.31
T_SDA: J4.3, R24.2, U1.11
U0RXD: TP11.1, U1.36
U0TXD: TP10.1, U1.37
USB_DN: J1.A7, J1.B7, U1.13, U2.3, U2.4
USB_DP: J1.A6, J1.B6, U1.14, U2.1, U2.6
VBAT: C5.1, J2.1, Q1.3, R9.1, TP6.1, U3.5
VBAT_ADC: C8.1, R9.2, R10.1, U1.39
VBUS: C4.1, C14.1, C15.1, D1.2, D3.1, J1.A4, J1.A9, J1.B4, J1.B9, R8.1, TP15.1, U2.5, U3.4, U3.8
VBUS_G: Q1.1, R7.1, R8.2
VIB_SW: R23.1, TP4.1, U1.6
VSYS: C6.1, C13.1, D1.1, D2.1, J5.1, Q1.2, TP1.1, TP14.1, U4.1, U4.3

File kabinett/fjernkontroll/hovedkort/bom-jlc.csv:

Comment,Designator,Footprint,LCSC Part #
100uF,C13,C_1210_3225Metric,sjekk: søk «100uF C»
100nF,"C2,C8,C10,C11,C12,C14,C15",C_0402_1005Metric,C1525 (sjekk)
10uF,"C1,C4,C5,C7,C9",C_0603_1608Metric,C19702 (sjekk)
1uF,"C3,C6",C_0402_1005Metric,C52923 (sjekk)
B5819W,"D1,D2,D3",D_SOD-123,C8598 (sjekk)
TYPE-C-31-M-12,J1,USB_C_Receptacle_HRO_TYPE-C-31-M-12,C165948 (sjekk)
S2B-PH-SM4-TB,J2,JST_PH_S2B-PH-SM4-TB_1x02-1MP_P2.00mm_Horizontal,sjekk: søk «S2B-PH-SM4-TB JST»
FH12-18S-0.5SH,J3,Hirose_FH12-18S-0.5SH_1x18-1MP_P0.50mm_Horizontal,sjekk: søk «FH12-18S-0.5SH Hirose»
FH12-6S-0.5SH,J4,Hirose_FH12-6S-0.5SH_1x06-1MP_P0.50mm_Horizontal,sjekk: søk «FH12-6S-0.5SH Hirose»
SM05B-SRSS-TB,J5,JST_SH_SM05B-SRSS-TB_1x05-1MP_P1.00mm_Horizontal,sjekk: søk «SM05B-SRSS-TB JST»
AO3401A,"Q1,Q2",SOT-23,C15127 (sjekk)
AO3400A,"Q3,Q4,Q5",SOT-23,C20917 (sjekk)
100k,"R7,R11,R13,R20,R22,R27",R_0402_1005Metric,C25741 (sjekk)
10R,R14,R_0402_1005Metric,C25077 (sjekk)
100R,"R12,R19",R_0402_1005Metric,C25076 (sjekk)
1k,R21,R_0402_1005Metric,C11702 (sjekk)
1M,"R9,R10,R23",R_0402_1005Metric,C26083 (sjekk)
4.7k,"R15,R16,R24,R25",R_0402_1005Metric,C25900 (sjekk)
68k,R26,R_0402_1005Metric,sjekk: søk «68k R»
5.1k,"R3,R4",R_0402_1005Metric,C25905 (sjekk)
2.4k,R5,R_0402_1005Metric,sjekk: søk «2.4k R»
10k,"R1,R2,R6,R17,R18",R_0402_1005Metric,C25744 (sjekk)
0R,R8,R_0402_1005Metric,sjekk: søk «0R R»
PTS810 RESET,SW44,SW_SPST_PTS810,sjekk: søk «PTS810 SW»
PTS810 BOOT,SW45,SW_SPST_PTS810,sjekk: søk «PTS810 SW»
ESP32-S3-WROOM-1-N4R2,U1,ESP32-S3-WROOM-1,sjekk: søk «ESP32-S3-WROOM-1-N4R2 ESP32-S3-WROOM-1»
USBLC6-2SC6,U2,SOT-23-6,C7519 (sjekk)
TP4056,U3,SOIC-8-1EP_3.9x4.9mm_P1.27mm_EP2.41x3.3mm,C16581 (sjekk)
RT9080-33GJ5,U4,SOT-23-5,sjekk: søk «RT9080-33GJ5 SOT-23-5»
TCA9555PWR,"U5,U6,U7",TSSOP-24_4.4x7.8mm_P0.65mm,sjekk: søk «TCA9555PWR TSSOP-24»

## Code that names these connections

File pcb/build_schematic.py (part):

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        ("A6", "D+", "passive", "R"), ("B6", "D+", "passive", "R"), ("A7", "D-", "passive", "R"), ("B7", "D-", "passive", "R"),
        ("A1", "GND", "passive", "B"), ("B1", "GND", "passive", "B"), ("A12", "GND", "passive", "B"), ("B12", "GND", "passive", "B"), ("S1", "SHIELD", "passive", "B")],
        keywords="usb-c receptacle")
    rpi = ["3V3", "5V", "GPIO2/SDA1", "5V", "GPIO3/SCL1", "GND", "GPIO4/GPCLK0", "GPIO14/TXD", "GND", "GPIO15/RXD", "GPIO17", "GPIO18/PCM_CLK",
           "GPIO27", "GND", "GPIO22", "GPIO23", "3V3", "GPIO24", "GPIO10/MOSI", "GND", "GPIO9/MISO", "GPIO25", "GPIO11/SCLK", "GPIO8/CE0",
           "GND", "GPIO7/CE1", "GPIO0/ID_SD", "GPIO1/ID_SC", "GPIO5", "GND", "GPIO6", "GPIO12/PWM0", "GPIO13/PWM1", "GND", "GPIO19/PCM_FS",
           "GPIO16", "GPIO26", "GPIO20/PCM_DIN", "GND", "GPIO21/PCM_DOUT"]
    S["RaspberryPi_40pin"] = ic("RaspberryPi_40pin", "Raspberry Pi 40-pinners GPIO-header (2x20, flatkabel) med BCM-pinnenavn",
        "Connector_PinHeader_2.54mm:PinHeader_2x20_P2.54mm_Vertical",
        [(str(i + 1), rpi[i], "passive", "L" if i % 2 == 0 else "R") for i in range(40)], keywords="raspberry pi gpio header")
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
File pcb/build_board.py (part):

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net(GND, ("J7", 6), *[(f"C{57+i}", 2) for i in range(5)])
# EXP: A5 = jack-deteksjon, A6 = HP EN (også på J22)
net("EXP_A5", ("U12", 26), ("J22", 1)); net("EXP_A6", ("U12", 27), ("J22", 2)); net("EXP_A7", ("U12", 28), ("J22", 3)); net("EXP_B5", ("U12", 6), ("J22", 4)); net(GND, ("J22", 6))
# overtemperaturvakt (NTC): 3V3 - R81 - NTC - GND; node -> U14 inngang (pinne 2), utgang (pinne 4) -> EXP_A7 = MCP GPA7
net("NTC", ("J24", 1), ("R81", 2), ("C112", 1), ("U14", 2)); net("EXP_B5", ("U14", 4), ("R82", 1)); net(GND, ("R82", 2))   # GPB5 – GPA7/GPB7 kan ikke brukes som innganger (Microchip-errata)
net("3V3", ("R81", 1), ("U14", 5), ("C111", 1), ("R83", 1)); net(GND, ("J24", 2), ("C112", 2), ("C111", 2), ("U14", 3))
# knapp bak -> GPIO 15
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# I2S: PCM1808 er master (BCK/LRCK), Pi slave, DAC slave
net("I2S_BCK", ("J5", 12), ("U4", 13), ("U10", 8)); net("I2S_LRCK", ("J5", 35), ("U4", 15), ("U10", 7)); net("I2S_DIN", ("J5", 40), ("U4", 14)); net("I2S_ADC", ("J5", 38), ("U10", 9))
# DAC
net("DAC_CAPP", ("U4", 2), ("C17", 1)); net("DAC_CAPM", ("U4", 4), ("C17", 2)); net("DAC_VNEG", ("U4", 5), ("C18", 1)); net("DAC_LDOO", ("U4", 18), ("C19", 1))   # PCM5102A pinne 18 = LDOO (TI SLAS859C), pinne 10 = DEMP
net(GND, ("U4", 3), ("U4", 9), ("U4", 10), ("U4", 11), ("U4", 12), ("U4", 16), ("U4", 19), ("C18", 2), ("C19", 2), ("C20", 2), ("C21", 2), ("C22", 2), ("C23", 2), ("C24", 2))
net("DAC_L", ("U4", 6), ("R8", 1)); net("DAC_R", ("U4", 7), ("R9", 1))
net("DAC_L_F", ("R8", 2), ("C23", 1), ("C25", 1)); net("DAC_R_F", ("R9", 2), ("C24", 1), ("C26", 1))
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net(GND, ("C46", 2), ("C48", 2), ("U6", 1), ("U6", 9), ("U6", 12), ("U6", 13), ("U6", 14), ("U6", 15), ("U6", 22), ("U6", 25), ("U6", 28), ("U6", 33),
    ("C36", 2), ("C37", 2), ("C38", 2), ("C39", 2), ("C40", 2), ("C41", 2), ("C42", 2), ("C43", 2), ("C44", 2), ("R16", 2), ("R18", 2), ("R20", 2))
net("GVDD", ("U6", 7), ("C44", 1), ("R15", 1), ("R17", 1)); net("AMP_GAIN", ("U6", 8), ("R15", 2), ("R16", 1)); net("AMP_PLIMIT", ("U6", 6), ("R17", 2), ("R18", 1))
net("AMP_SDZ", ("U6", 2), ("R19", 2), ("R20", 1))   # pinne 1 MODSEL = GND (BD), 12 MUTE = GND, 13-15 AM = GND, 16 SYNC åpen (utgang)
net("BSNL", ("U6", 20), ("C32", 1)); net("BSPL", ("U6", 24), ("C33", 1)); net("BSNR", ("U6", 26), ("C34", 1)); net("BSPR", ("U6", 30), ("C35", 1))
net("OUTNL", ("U6", 21), ("C32", 2), ("L2", 1), ("R21", 1)); net("OUTPL", ("U6", 23), ("C33", 2), ("L3", 1), ("R22", 1))
net("OUTNR", ("U6", 27), ("C34", 2), ("L4", 1), ("R23", 1)); net("OUTPR", ("U6", 29), ("C35", 2), ("L5", 1), ("R24", 1))
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net(GND, ("U7", 1), ("Y1", 2), ("Y1", 4), ("R75", 2), ("C66", 2), ("C67", 2), ("C68", 2), ("C69", 2), ("C73", 2), ("C70", 2), ("U8", 5), ("U8", 6), ("R47", 2))
net("USB_UP_DP", ("U7", 16), ("U8", 8)); net("USB_UP_DM", ("U7", 15), ("U8", 7))
net("USB_SEL", ("U12", 5), ("U8", 9), ("R47", 1))   # MCP GPB4: lav = PC 1, høy = PC 2
net("PC1_DP", ("U8", 1), ("J11", "A6"), ("J11", "B6"), ("D10", 1), ("D10", 6)); net("PC1_DM", ("U8", 2), ("J11", "A7"), ("J11", "B7"), ("D10", 3), ("D10", 4))
net("PC2_DP", ("U8", 3), ("J12", "A6"), ("J12", "B6"), ("D11", 1), ("D11", 6)); net("PC2_DM", ("U8", 4), ("J12", "A7"), ("J12", "B7"), ("D11", 3), ("D11", 4))
# VBUS-padene på USB-C er ikke i bruk (huben går på egen 5 V). A4/B9 og A9/B4 er fysisk samme pad – gi hvert par sitt nett,
# så KiCad verken melder klaring (pads uten nett) eller krever et spor mellom dem.
for _j, _n in (("J11", "PC1"), ("J12", "PC2")):
    net(f"{_n}_VBUS_A", (_j, "A4"), (_j, "B9")); net(f"{_n}_VBUS_B", (_j, "A9"), (_j, "B4"))
net("PC1_CC1", ("J11", "A5"), ("R48", 1)); net("PC1_CC2", ("J11", "B5"), ("R49", 1)); net("PC2_CC1", ("J12", "A5"), ("R50", 1)); net("PC2_CC2", ("J12", "B5"), ("R51", 1))
net(GND, ("R48", 2), ("R49", 2), ("R50", 2), ("R51", 2), *[(j, p) for j in ("J11", "J12") for p in ("A1", "B1", "A12", "B12", "S1")])
for i, (dp, dm) in enumerate(((11, 10), (9, 8), (7, 6), (5, 4))):
    net(f"USB{i+1}_DP", ("U7", dp), (f"J{15+i}", 3), (f"D{6+i}", 1), (f"D{6+i}", 6)); net(f"USB{i+1}_DM", ("U7", dm), (f"J{15+i}", 2), (f"D{6+i}", 3), (f"D{6+i}", 4)); net(GND, (f"J{15+i}", 4), (f"J{15+i}", 5))
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    ("24V_AMP", "F.Cu", 2.0, [(100, 20), (121.8, 20), (121.8, 23.2), (135.8, 23.2), (135.8, 20)]), ("24V_AMP", "F.Cu", 2.0, [(131.0, 23.2), (131.0, 24.6)]),     # K1.1 -> C40 -> C41
    ("24V_AMP", "F.Cu", 0.8, [(129.3, 23.2), (129.3, 29.45)]), ("24V_AMP", "F.Cu", 0.6, [(129.3, 29.45), (128.0, 29.45)]),   # PVCC pinne 31/32
    ("24V_AMP", "B.Cu", 1.2, [(131.0, 23.2), (131.0, 38.2)]), ("24V_AMP", "F.Cu", 0.8, [(131.0, 38.2), (128.9, 38.2)]),        # PVCC pinne 17–19 via undersiden
    ("24V_AMP", "F.Cu", 0.5, [(128.9, 37.58), (128.9, 39.1)]),   # smalere/kortere så BSNL (pinne 20) får plass over
    ("24V_AMP", "F.Cu", 0.4, [(127.65, 37.58), (128.9, 37.58)]), ("24V_AMP", "F.Cu", 0.4, [(127.65, 38.23), (128.9, 38.23)]), ("24V_AMP", "F.Cu", 0.4, [(127.65, 38.88), (128.9, 38.88)]),
    ("5V", "F.Cu", 1.5, [(89.55, 30), (89.55, 34.2), (96.5, 34.2), (96.5, 51.77)]),                      # buck -> kondensatorrekke (C8–C11 står med padene 2,7 mm brede i x)
    ("5V", "F.Cu", 0.8, [(94.0, 39.48), (96.5, 39.48)]), ("5V", "F.Cu", 0.8, [(94.0, 43.98), (96.5, 43.98)]), ("5V", "F.Cu", 0.8, [(94.0, 48.48), (96.5, 48.48)]), ("5V", "F.Cu", 0.8, [(94.0, 51.77), (96.5, 51.77)]),
    ("5V", "F.Cu", 1.5, [(89.55, 34.2), (86.0, 34.2), (83.46, 36.8), (82.0, 38.26), (82.0, 43.0)]),                   # -> J6 (5 V til Pi)
    ("5V", "B.Cu", 1.2, [(82.0, 43.0), (60.6, 43.0), (51.25, 43.0), (50.79, 42.54), (49.54, 42.54)]),   # J6 -> Pi-header J5.4 (5 V) under, matet fra samme skinne
]
POWER_SPINE_VIAS = [("VIN24", (58.96, 21.5), 1.3, 0.75), ("VIN24", (58.96, 23.2), 1.0, 0.5), ("24V_AMP", (131.0, 23.2), 1.3, 0.75), ("24V_AMP", (131.0, 24.6), 1.0, 0.5), ("24V_AMP", (131.0, 38.2), 1.3, 0.75)]   # store/doble vias: via-veggen var flaskehalsen for 24V_AMP
FIXED_TRACKS = POWER_SPINE + [("OUTNL", "F.Cu", 0.4, [(127.65, 36.275), (137.05, 36.275), (137.05, 36.9)]),   # TPA3116 pinne 21 -> C32.2 (utvides i export)
                ("BSPL", "F.Cu", 0.3, [(127.65, 34.325), (133.05, 34.325)]),   # pinne 24 -> C33.1
                ("OUTPL", "F.Cu", 0.4, [(127.65, 34.975), (128.6, 34.975), (129.1, 35.475), (134.3, 35.475), (134.95, 34.825), (134.95, 34.3)]),   # pinne 23 -> C33.2 under C33.1
    ("5V", "F.Cu", 0.3, [(132.25, 43.5625), (132.25, 42.1), (135.8, 42.1), (136.22, 43.8)]),   # TPA6132A2 VDD (pinne 14) -> C100
    ("HP_INR", "F.Cu", 0.2, [(130.5625, 45.75), (129.4, 45.72)]),   # TPA6132A2 pinne 4: fast utgang til via, ellers stenges den inne

    ("CODEC_VINR", "F.Cu", 0.25, [(150.4, 87.575), (148.9, 87.575)]), ("CODEC_VINR", "B.Cu", 0.25, [(148.9, 87.575), (148.9, 88.9), (155.0, 88.9)]),   # PCM2900C pinne 13 -> C98
    ("CODEC_VINR", "F.Cu", 0.25, [(155.0, 88.9), (155.0, 89.54), (160.0, 89.54), (161.0, 89.3), (170.95, 89.3), (170.95, 88.0)]),
    ("HP_CPP", "F.Cu", 0.2, [(133.438, 44.75), (133.85, 44.75), (134.05, 44.95), (134.9, 46.0)]),
    ("RLY_LOW", "F.Cu", 0.25, [(105.175, 42.0), (105.3, 43.3)]), ("RLY_LOW", "B.Cu", 0.25, [(105.3, 43.3), (101.5, 35.3)]),   # R54 -> Q7 via B.Cu (AMP_SD_G og Q8_GATE sperrer på F.Cu)
    ("RLY_LOW", "F.Cu", 0.25, [(101.5, 35.3), (101.138, 34.0)]),   # TPA6132A2 pinne 11 -> C103 (trangt mellom HP_VDD og HP_CPN)
    ("AMP_RINN", "F.Cu", 0.2, [(120.35, 31.725), (118.6, 31.725)]),   # TPA3116 pinne 5 ble stengt inne av nabosporene
                ("GND", "F.Cu", 0.2, [(133.438, 45.25), (132.5, 45.0)]), ("GND", "F.Cu", 0.2, [(131.75, 43.562), (131.75, 44.7)]),   # TPA6132A2 PGND/SGND -> termisk pad
                ("BSNL", "F.Cu", 0.3, [(127.65, 36.925), (136.0, 36.925), (136.0, 38.1), (138.95, 38.1), (138.95, 37.3)])]   # pinne 20 -> C32.1 (rundt under C32.2)   # FE1.1s pinne 7 ut nedover mellom nabosporene
FIXED_VIAS = [("HP_INR", (129.4, 45.72)), ("CODEC_VINR", (148.9, 87.575)), ("CODEC_VINR", (155.0, 88.9)), ("RLY_LOW", (105.3, 43.3)), ("RLY_LOW", (101.5, 35.3)), ("AMP_RINN", (118.6, 31.725))]
FIXED_GND_VIP = {}   # GND rutes nå som nett av Freerouting – ingen via-i-pad (lodder dårlig uten fylte vias)   # via-i-pad (0,45/0,2) på GND-pinner som er omringet av signaler (PCM5102A pinne 3)

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
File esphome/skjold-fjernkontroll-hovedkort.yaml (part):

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#     7 × 5 brytere, og select-entiteten «Tasteoppsett» velger hvilken bryter som er hvilken tast (fra taster.py).
#   · Meny-tasten: kort trykk = enhetssiden (apper/innganger/spiller), langt trykk = Skjold-spilleren.
#     Skjold-tasten: kort = Start, langt = velg enhet.
#   · Dyp søvn etter ${sovn_etter} uten bruk. Vekkes av en tast (TCA9555 INT → GPIO7) eller av at du løfter den
#     (vibrasjonsbryter → GPIO6).
#
# Pinnene følger hovedkortet (kabinett/fjernkontroll/hovedkort/kretser.py, pinnetabellen i LES_MEG.md). IKKE TESTET PÅ MASKINVARE.
# Blokkene mellom «# >>> …» og «# <<< …» lages av kabinett/fjernkontroll/taster.py.
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  on_boot:
    - priority: 600
      then:
        - output.turn_on: strom_skjerm         # 3V3 til skjerm og IR-mottaker (AO3401, GPIO15)
        - light.turn_on: { id: baklys, brightness: !lambda "return id(lysstyrke) / 100.0f;" }
        - script.execute: sovn_teller
        - lambda: |-
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# ---------- busser og I/O ----------
i2c:
  - id: bus_a                        # 3 × TCA9555 (4,7 kΩ til 3V3)
    sda: GPIO8
    scl: GPIO9
    frequency: 400kHz
    scan: false
  - id: bus_b                        # berøring (FT6336U, 0x38) – egen buss, så skjermen kan slås helt av i søvn
    sda: GPIO18
    scl: GPIO38                      # pull-up til 3V3_SW: bussen er død når skjermstrømmen er av
    frequency: 400kHz
    scan: false
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  - { id: tca_c, i2c_id: bus_a, address: 0x22 }

spi:
  clk_pin: GPIO12
  mosi_pin: GPIO11

output:
  - platform: ledc
    id: baklys_pwm
    pin: GPIO21                      # → AO3400 (Q3) på LED-katoden
  - platform: gpio
    id: strom_skjerm
    pin: { number: GPIO15, inverted: true }   # AO3401 (Q2), lav = på (100 kΩ holder den av i søvn)
  - platform: gpio
    id: vibrator
    pin: GPIO16                      # → 1 kΩ → AO3400 (Q5) → motoren

light:
  - platform: monochromatic
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  - platform: ili9xxx
    id: skjerm
    model: ST7789V
    dc_pin: GPIO13
    reset_pin: GPIO14
    invert_colors: true              # IPS-paneler; sett false hvis fargene er negative
    color_order: rgb                 # bytt til bgr hvis rødt og blått er byttet om
    dimensions: { width: 240, height: 320 }
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    address: 0x38
    id: beroring
    i2c_id: bus_b
    interrupt_pin: GPIO10
    reset_pin: GPIO2
    display: skjerm
    on_touch:
      - script.execute: sovn_teller
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# ---------- IR ----------
remote_transmitter:
  id: ir_tx
  pin: GPIO4                         # → 100 Ω → AO3400 (Q4) → 3 × IR-diode 940 nm på IR-kortet
  carrier_duty_percent: 33%
  non_blocking: true

remote_receiver:
  id: ir_rx
  pin: { number: GPIO5, inverted: true }    # VS1838B (aktiv lav)
  dump: []
  tolerance: 25%
  on_nec:
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# ---------- søvn ----------
deep_sleep:
  id: dyp_sovn
  wakeup_pin: { number: GPIO7, inverted: true, mode: { input: true } }   # TCA9555 INT (felles, 10 kΩ til 3V3)
  wakeup_pin_mode: KEEP_AWAKE
  esp32_ext1_wakeup:
    pins: [ { number: GPIO6, allow_other_uses: true } ]   # vibrasjonsbryter SW-18010P mellom 3V3 og GPIO6 (1 MΩ ned)
    mode: ANY_HIGH

switch:
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  - platform: adc
    id: batteri_v
    name: Batterispenning
    pin: GPIO1                       # VBAT via 2 × 1 MΩ og 100 nF
    attenuation: 12db
    update_interval: 30s
    filters: [ { multiply: 2.0 }, { sliding_window_moving_average: { window_size: 4, send_every: 1 } } ]
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  - platform: gpio
    id: lader
    name: Lader
    pin: { number: GPIO17, inverted: true }   # TP4056 CHRG (åpen drain, 10 kΩ til 3V3; lav = lader)
    device_class: battery_charging
  - platform: gpio
    id: loftet
    internal: true
    pin: { number: GPIO6, mode: { input: true }, allow_other_uses: true }
    on_press:
      - script.execute: sovn_teller
  - platform: gpio
    id: dokket
    name: I dokken
    icon: mdi:cradle-outline
    pin: { number: GPIO40, mode: { input: true } }   # pogo + (POGO) via R26 68 kΩ / R27 100 kΩ (høy = i dokken)
    filters: [ { delayed_on: 400ms }, { delayed_off: 300ms } ]
    on_press: [ script.execute: dokk_inn ]
    on_release: [ script.execute: dokk_ut ]
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    then:
      - lambda: |-
          struct Akt { const char *navn; int enhet; const char *tv; int inn; const char *proj; const char *atv;
                       const char *app; const char *skj; const char *scene; };
          static const Akt A[6] = {
            {"${akt1_navn}", ${akt1_enhet}, "${akt1_tv}", ${akt1_inngang}, "${akt1_projektor}", "${akt1_atv}", "${akt1_app}", "${akt1_skjold}", "${akt1_scene}"},
            {"${akt2_navn}", ${akt2_enhet}, "${akt2_tv}", ${akt2_inngang}, "${akt2_projektor}", "${akt2_atv}", "${akt2_app}", "${akt2_skjold}", "${akt2_scene}"},
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          lv_label_set_text(id(lbl_mini_ini), skjold::initialer(aa.empty() ? std::string("Apple TV") : aa).c_str());
          lv_obj_set_style_bg_color(id(mini_flis), lv_color_hex(skjold::flisfarge(aa.empty() ? std::string("Apple TV") : aa)), 0);
          // Start-kortet for valgt enhet
          if (e == 1) { t = lv_label_get_text(id(lbl_mini_t)); u = lv_label_get_text(id(lbl_mini_u)); prog = aprog; spill = tilst == "playing"; tidtekst = atid; }
          else if (e == 2) { t = id(tittel) == "Skjold" && skjold::rtc_skjold_tittel[0] ? skjold::rtc_skjold_tittel : id(tittel);
                             u = id(artist).empty() ? std::string(skjold::rtc_skjold_artist) : id(artist);
                             if (!id(skjold_paa)) u = "Av"; spill = id(spiller); }
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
